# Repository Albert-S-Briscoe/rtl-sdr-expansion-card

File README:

TODO.

See https://community.frame.work/t/rtl-sdr-expansion-card/37098

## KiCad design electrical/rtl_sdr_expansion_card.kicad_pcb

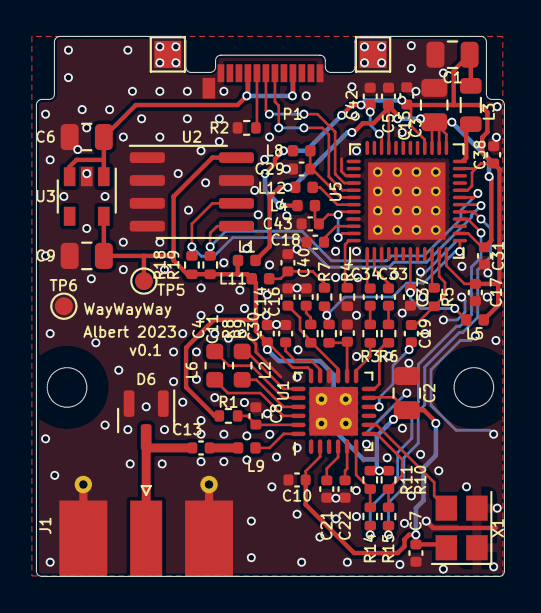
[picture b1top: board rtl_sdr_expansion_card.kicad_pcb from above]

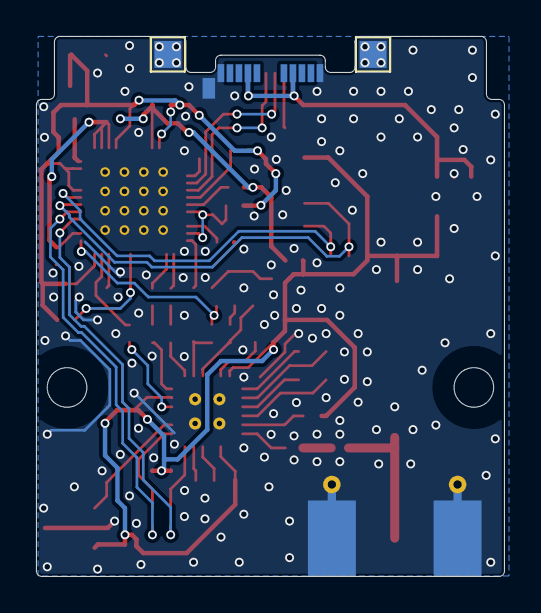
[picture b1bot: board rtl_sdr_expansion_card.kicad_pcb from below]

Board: 2 copper layers, 26.0 x 30.0 mm, 71 parts (2 on the bottom side), 47 nets.

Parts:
C1: 47µF; C_0805_2012Metric
C2, C3: 10µF; C_0805_2012Metric
C4, C5, C7, C10, C11, C15, C17, C18, C19, C22, C29, C30, C31, C33, C34, C37, C38, C40, C42, C43: 100nF; C_0402_1005Metric
C6, C9: 10uF; C_0805_2012Metric
C8, C13: 10nF; C_0402_1005Metric
C14: 330pF; C_0402_1005Metric
C16: 6.8nF; C_0402_1005Metric
C21: 1µF; C_0402_1005Metric
D6: BAV99; SOT-23
H1, H2: MountingHole; MountingHole_2.2mm_M2
J1: Conn_Coaxial; SMA_Molex_73251-2120_EdgeMount_Horizontal
L1, L4, L5, L8, L11, L12: bead; L_0402_1005Metric
L2, L6: 150nH; L_0603_1608Metric
L3: 4.7µH; L_0805_2012Metric
L9: ?; L_0402_1005Metric
P1: USB_C_Plug_USB2.0; FW_USB_C_Plug_Molex_105444
R1: ~5.6Ω; R_0402_1005Metric
R2: 5.1k; R_0402_1005Metric
R3, R6: 100Ω; R_0402_1005Metric
R4, R9: 10k; R_0402_1005Metric
R5: 1MΩ; R_0402_1005Metric
R7, R10, R11, R18, R19: 4.7k; R_0402_1005Metric
R8: 1.8k; R_0402_1005Metric
R14, R15: 220Ω; R_0402_1005Metric
TP1, TP2, TP3, TP4: TestPoint; TestPoint_Pad_1.5x1.5mm
TP5, TP6: TestPoint; TestPoint_Pad_D1.0mm
U1: QFN-24_EP_4x4_Pitch0.5mm_vias0.3mm
U2: M24C02-WMN; SOIC-8_3.9x4.9mm_P1.27mm
U3: AP2112K-3.3; SOT-23-5
U5: QFN-48_EP_6x6_Pitch0.4mm_vias0.3mm
X1: Crystal_SMD_3225-4Pin_3.2x2.5mm

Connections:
+1V2: C1.2, C15.1, C17.1, C38.1, C42.1, L3.2, L4.1, L5.1, L8.1, U5.12 (1.2V), U5.20 (1.2V), U5.23 (1.2V), U5.28 (1.2V), U5.34 (1.2V)
+3V3: C2.1, C4.1, C7.2, C9.1, C10.2, L1.2, L11.2, R1.1, R10.1, R11.1, R18.1, R19.1, TP5.1, U1.2 (VCC), U1.11 (VCC), U1.18 (VCC), U2.8 (VCC), U3.5 (VOUT), X1.4 (Vcc)
/RTL2832U/1V2_FILT_1: C43.2, L4.2, U5.44 (1.2V), U5.47 (1.2V)
/RTL2832U/1V2_FILT_2: C37.1, L5.2, U5.7 (1.2V)
/RTL2832U/1V2_FILT_3: C29.2, L8.2, U5.42 (1.2V)
/RTL2832U/EEPROM_SCL: R18.2, U2.6 (SCL), U5.18 (EEPROM_SCL)
/RTL2832U/EEPROM_SDA: R19.2, U2.5 (SDA), U5.19 (EEPROM_SDA)
/RTL2832U/IF_I_N: C33.2, U5.2 (I_IN-)
/RTL2832U/IF_I_P: C34.2, U5.1 (I_IN+)
/RTL2832U/RTL_3V3: C3.1, C5.1, C31.1, L1.1, L12.1, U5.14 (3.3V), U5.25 (3.3V), U5.26 (3.3V), U5.27 (3.3V), U5.33 (3.3V)
/USBC_CC: P1.A5 (CC), R2.1
GND: C1.1, C2.2, C3.2, C4.2, C5.2, C6.2, C7.1, C8.1, C9.2, C10.1, C11.2, C14.2, C15.2, C16.2, C17.2, C18.1, C21.1, C22.1, C29.1, C30.2, C31.2, C37.2, C38.2, C40.2, C42.2, C43.1, D6.1 (K), D6.2 (A), J1.2 (Ext), P1.A1 (GND), P1.A12 (GND), P1.B1 (GND), P1.B12 (GND), P1.S1 (SHIELD), R2.2, R4.1, TP1.1, TP2.1, TP3.1, TP4.1, TP6.1, U1.16 (GND), U1.25 (GND), U2.1 (E0), U2.2 (E1), U2.3 (E2), U2.4 (VSS), U2.7 (~WC), U3.2 (GND), U5.3 (GND), U5.8 (GND), U5.39 (GND), U5.45 (GND), U5.49 (GND), X1.1 (GND/NC), X1.2 (GND)
IF_AGC: R7.2, R9.2, U5.13 (AGC1)
IF_N: R6.1, U1.12 (IF_N)
IF_P: R3.1, U1.13 (IF_P)
unnamed: C8.2, R1.2, U1.23 (VCC)
unnamed: C13.2, L9.1
unnamed: C16.1, R8.2
unnamed: C33.1, R6.2
unnamed: C34.1, R3.2
unnamed: C40.1, L11.1, R7.1
unnamed: C13.1, D6.3 (K), J1.1 (In)
unnamed: L12.2, U5.43 (3.3V)
unnamed: C19.1, U1.10 (CLK_Out)
unnamed: C14.1, R8.1, U1.15 (CP)
unnamed: C21.2, U1.4 (Det1)
unnamed: C22.2, U1.5 (Det2)
unnamed: C30.1, R9.1, U1.14 (IF_AGC)
unnamed: L9.2, U1.24 (RF_IN)
unnamed: R11.2, R14.1, U1.6 (SCL)
unnamed: R10.2, R15.1, U1.7 (SDA)
unnamed: L2.1, U1.21 (TF1N)
unnamed: L6.1, U1.22 (TF1P)
unnamed: L2.2, U1.19 (TF2N)
unnamed: L6.2, U1.20 (TF2P)
unnamed: C11.1, U1.17 (VDD_PLL)
unnamed: U1.8 (Xtal_I), X1.3 (Out)
unnamed: L3.1, U5.24 (1.2V_REG_OUT)
unnamed: C18.2, U5.46 (C)
unnamed: R4.2, U5.48 (R)
unnamed: R5.2, U5.10 (X_O)
RTL_CLK: C19.2, R5.1, U5.11 (X_I)
T_SCL: R14.2, U5.16 (TUNER_SCL)
T_SDA: R15.2, U5.17 (TUNER_SDA)
USB_DN: P1.A7 (D-), U5.41 (USB_DM)
USB_DP: P1.A6 (D+), U5.40 (USB_DP)
VBUS: C6.1, P1.A4 (VBUS), P1.A9 (VBUS), P1.B4 (VBUS), P1.B9 (VBUS), U3.1 (VIN), U3.3 (EN)

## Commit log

2024-02-04 Initial commit: schematics, board layout, and printable case models

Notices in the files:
electrical/rtl_sdr_expansion_card.kicad_pcb:
This work is licensed under a Creative Commons Attribution 4.0 International License
